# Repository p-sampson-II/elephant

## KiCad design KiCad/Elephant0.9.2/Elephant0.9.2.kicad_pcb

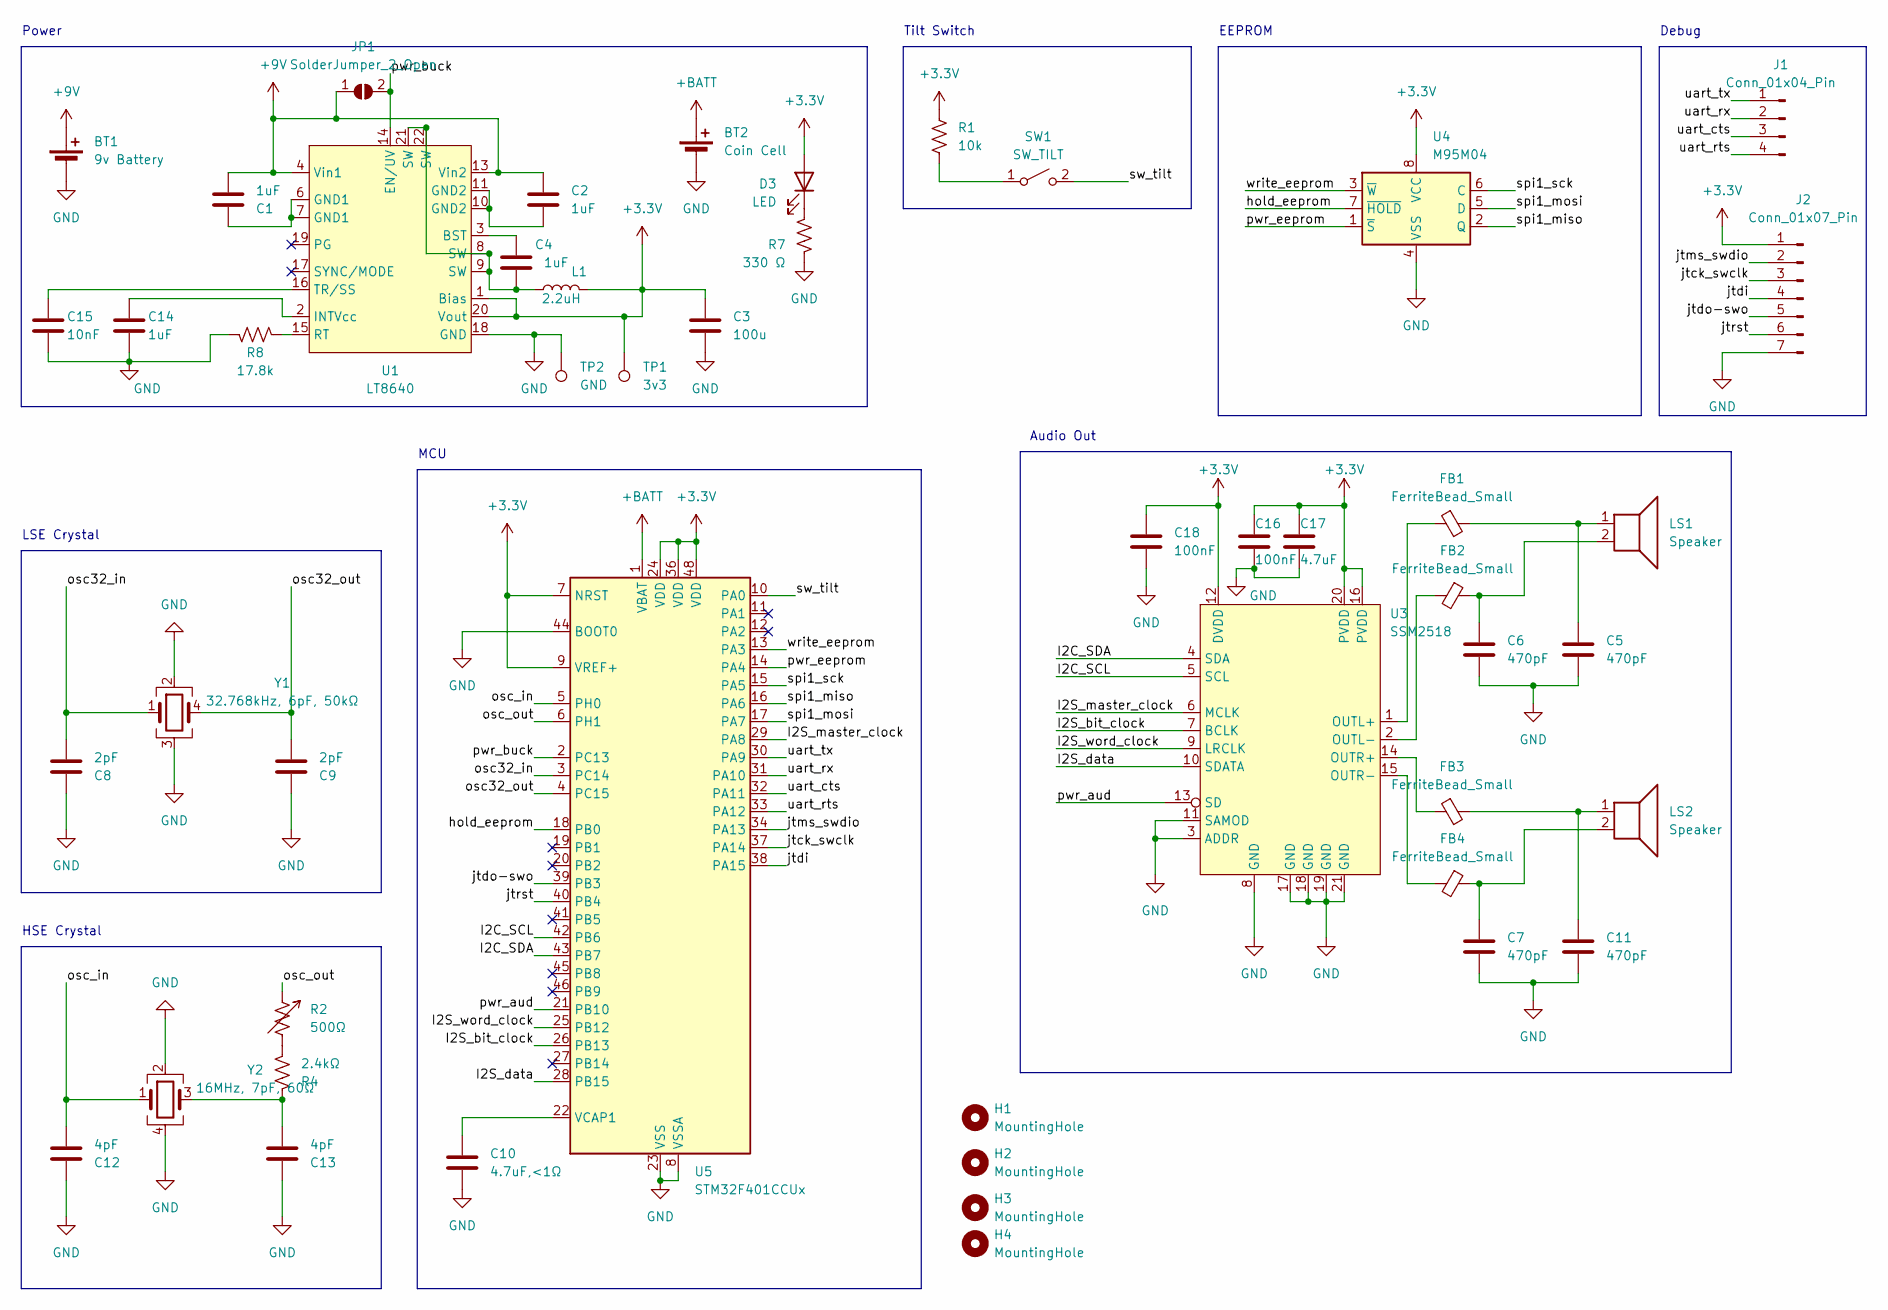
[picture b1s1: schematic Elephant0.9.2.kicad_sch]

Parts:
BT1: 9v Battery; JST_PH_B2B-PH-K_1x02_P2.00mm_Vertical
BT2: Coin Cell; BatteryHolder_Keystone_1057_1x2032
C1, C2, C4, C14: 1uF; C_0603_1608Metric
C3: 100u; Capacitor SMD 2917 (7343 Metric)
C5, C6, C7, C11: 470pF; C_0603_1608Metric
C8, C9: 2pF; C_0603_1608Metric
C10: 4.7uF,<1Ω; 1411 (3528 Metric)
C12, C13: 4pF; C_0603_1608Metric
C15: 10nF; C_0603_1608Metric
C16, C18: 100nF; C_0603_1608Metric
C17: 4.7uF; C_0603_1608Metric
D3: LED; LED_0603_1608Metric
FB1, FB2, FB3, FB4: FerriteBead_Small; L_0402_1005Metric
H1, H2, H3, H4: MountingHole; MountingHole_2.7mm_M2.5
J1: Conn_01x04_Pin; JST_PH_B4B-PH-K_1x04_P2.00mm_Vertical
J2: Conn_01x07_Pin; JST_PH_B7B-PH-K_1x07_P2.00mm_Vertical
JP1: SolderJumper_2_Open; SolderJumper-2_P1.3mm_Open_Pad1.0x1.5mm
L1: 2.2uH; L_Bourns-SRN8040_8x8.15mm
LS1, LS2: Speaker; JST_PH_B2B-PH-K_1x02_P2.00mm_Vertical
R1: 10k; R_0603_1608Metric
R2: 500Ω; TC42 – 2 mm SMD Trimpot - Bournes
R4: 2.4kΩ; R_0603_1608Metric
R7: 330 Ω; R_0603_1608Metric
R8: 17.8k; R_0603_1608Metric
SW1: SW_TILT; PinHeader_1x02_P2.54mm_Vertical
TP1: 3v3; TestPoint_Pad_D1.0mm
TP2: GND; TestPoint_Pad_D1.0mm
U1: LT8640
U3: SSM2518; QFN-20-1EP_4x4mm_P0.5mm_EP2.5x2.5mm
U4: M95M04; TSSOP-8_4.4x3mm_P0.65mm
U5: STM32F401CCUx; QFN-48-1EP_7x7mm_P0.5mm_EP5.6x5.6mm
Y1: 32.768kHz, 6pF, 50kΩ; Crystal_SMD_Abracon_ABS25-4Pin_8.0x3.8mm
Y2: 16MHz, 7pF, 60Ω; Crystal_SMD_3225-4Pin_3.2x2.5mm

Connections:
+3.3V: C3.1, C16.1, C17.1, C18.1, D3.2 (A), J2.1, L1.2, R1.1, TP1.1, U1.1 (Bias), U1.20 (Vout), U3.12 (DVDD), U3.16 (PVDD), U3.20 (PVDD), U4.8 (VCC), U5.7 (NRST), U5.9 (VREF+), U5.24 (VDD), U5.36 (VDD), U5.48 (VDD)
+9V: BT1.1 (+), C1.2, C2.1, JP1.1 (A), U1.4 (Vin1), U1.13 (Vin2)
+BATT: BT2.1 (+), U5.1 (VBAT)
/I2C_SCL: U3.5 (SCL), U5.42 (PB6)
/I2C_SDA: U3.4 (SDA), U5.43 (PB7)
/I2S_bit_clock: U3.7 (BCLK), U5.26 (PB13)
/I2S_data: U3.10 (SDATA), U5.28 (PB15)
/I2S_master_clock: U3.6 (MCLK), U5.29 (PA8)
/I2S_word_clock: U3.9 (LRCLK), U5.25 (PB12)
/hold_eeprom: U4.7 (~HOLD), U5.18 (PB0)
/jtck_swclk: J2.3, U5.37 (PA14)
/jtdi: J2.4, U5.38 (PA15)
/jtdo-swo: J2.5, U5.39 (PB3)
/jtms_swdio: J2.2, U5.34 (PA13)
/jtrst: J2.6, U5.40 (PB4)
/osc32_in: C8.2, U5.3 (PC14), Y1.1
/osc32_out: C9.2, U5.4 (PC15), Y1.4
/osc_in: C12.2, U5.5 (PH0), Y2.1
/osc_out: R2.1, U5.6 (PH1)
/pwr_aud: U3.13 (SD), U5.21 (PB10)
/pwr_buck: JP1.2 (B), U1.14 (EN/UV), U5.2 (PC13)
/pwr_eeprom: U4.1 (~S), U5.14 (PA4)
/spi1_miso: U4.2 (Q), U5.16 (PA6)
/spi1_mosi: U4.5 (D), U5.17 (PA7)
/spi1_sck: U4.6 (C), U5.15 (PA5)
/sw_tilt: SW1.2 (B), U5.10 (PA0)
/uart_cts: J1.3, U5.32 (PA11)
/uart_rts: J1.4, U5.33 (PA12)
/uart_rx: J1.2, U5.31 (PA10)
/uart_tx: J1.1, U5.30 (PA9)
/write_eeprom: U4.3 (~W), U5.13 (PA3)
GND: BT1.2 (-), BT2.2 (-), C3.2, C5.2, C6.2, C7.2, C8.1, C9.1, C10.2, C11.2, C12.1, C13.1, C14.2, C15.2, C16.2, C17.2, C18.2, J2.7, R7.2, R8.2, TP2.1, U1.18 (GND), U3.3 (ADDR), U3.8 (GND), U3.11 (SAMOD), U3.17 (GND), U3.18 (GND), U3.19 (GND), U3.21 (GND), U4.4 (VSS), U5.8 (VSSA), U5.23 (VSS), U5.35 (VSS), U5.44 (BOOT0), U5.47 (VSS), U5.49 (VSS), Y1.2, Y1.3, Y2.2, Y2.4
unnamed: C1.1, U1.6 (GND1), U1.7 (GND1)
unnamed: C2.2, U1.10 (GND2), U1.11 (GND2)
unnamed: C4.2, L1.1, U1.8 (SW), U1.9 (SW), U1.21 (SW), U1.22 (SW)
unnamed: C5.1, FB1.2, LS1.1
unnamed: C6.1, FB2.1, LS1.2
unnamed: C7.1, FB4.1, LS2.2
unnamed: C11.1, FB3.2, LS2.1
unnamed: C13.2, R4.1, Y2.3
unnamed: D3.1 (K), R7.1
unnamed: R2.2, R4.2
unnamed: R1.2, SW1.1 (A)
unnamed: C4.1, U1.3 (BST)
unnamed: C14.1, U1.2 (INTVcc)
unnamed: R8.1, U1.15 (RT)
unnamed: C15.1, U1.16 (TR/SS)
unnamed: FB1.1, U3.1 (OUTL+)
unnamed: FB2.2, U3.2 (OUTL-)
unnamed: FB3.1, U3.14 (OUTR+)
unnamed: FB4.2, U3.15 (OUTR-)
unnamed: C10.1, U5.22 (VCAP1)

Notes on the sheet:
HSE Crystal
MCU
Power
Debug
Audio Out
EEPROM
Tilt Switch
LSE Crystal

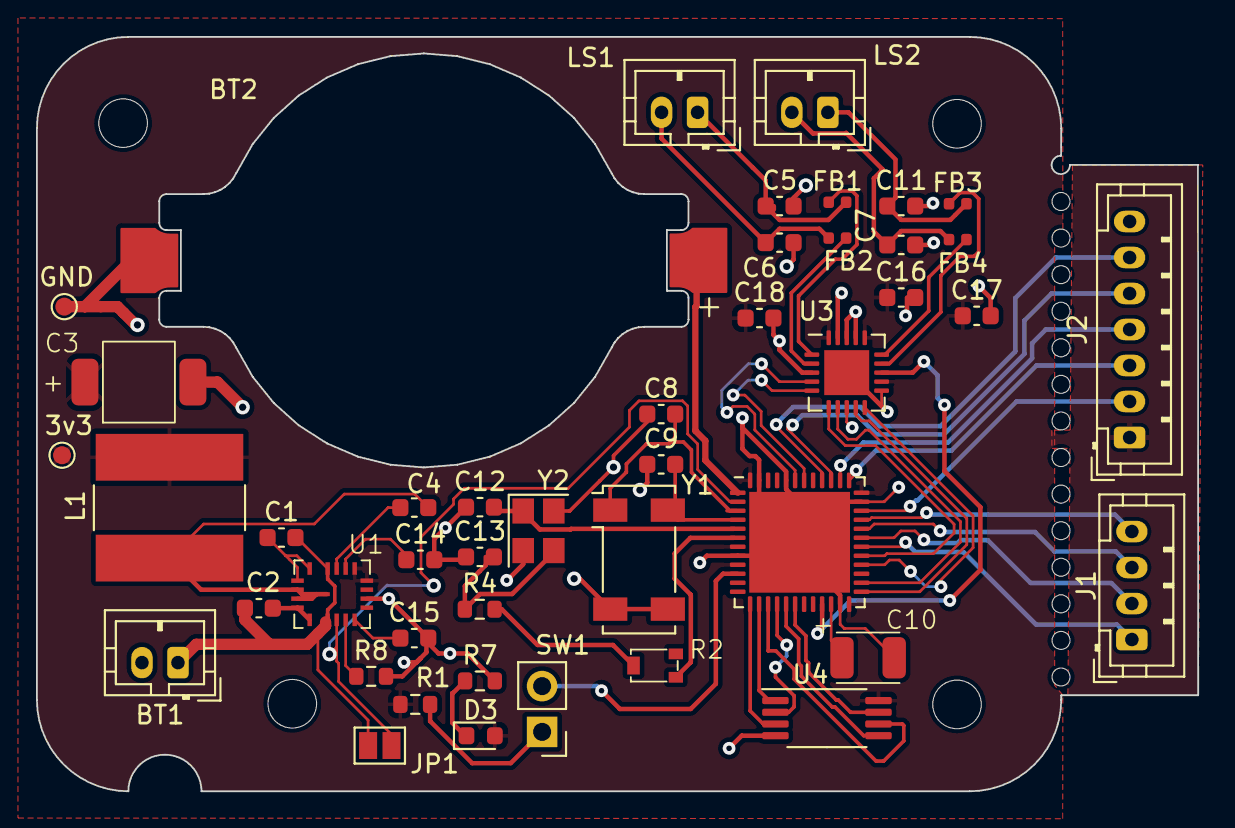
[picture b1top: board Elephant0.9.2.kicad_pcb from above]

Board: 2 copper layers, 64.5 x 41.9 mm, 49 parts (0 on the bottom side), 52 nets.

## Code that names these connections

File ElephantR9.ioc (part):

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Mcu.Name=STM32F401C(B-C)Ux
Mcu.Package=UFQFPN48
Mcu.UserName=STM32F401CCUx
PA0-WKUP.GPIOParameters=GPIO_Label
PA0-WKUP.GPIO_Label=sw_tilt
PA0-WKUP.Mode=SYS_WakeUp0
PA0-WKUP.Signal=SYS_WKUP
PA1.GPIOParameters=GPIO_Label
PA1.GPIO_Label=ld_heartbeat
PA1.Signal=GPIO_Output
PA10.Mode=Asynchronous
PA10.Signal=USART1_RX
PA11.Mode=CTS_RTS
PA11.Signal=USART1_CTS
PA12.Mode=CTS_RTS
PA12.Signal=USART1_RTS
PA13.Mode=JTAG_5_pins
PA13.Signal=SYS_JTMS-SWDIO
PA14.Mode=JTAG_5_pins
PA14.Signal=SYS_JTCK-SWCLK
PA15.Mode=JTAG_5_pins
PA15.Signal=SYS_JTDI
PA3.GPIOParameters=GPIO_Label
PA3.GPIO_Label=pwr_eeprom
PA3.Signal=GPIO_Output
PA4.GPIOParameters=GPIO_Label
PA4.GPIO_Label=write_eeprom
PA4.Signal=GPIO_Output
PA5.Mode=Full_Duplex_Master
PA5.Signal=SPI1_SCK
PA6.Mode=Full_Duplex_Master
PA6.Signal=SPI1_MISO
PA7.Mode=Full_Duplex_Master
PA7.Signal=SPI1_MOSI
PA8.Mode=Clock-out-1
PA8.Signal=RCC_MCO_1
PA9.Mode=Asynchronous
PA9.Signal=USART1_TX
PB0.GPIOParameters=GPIO_Label
PB0.GPIO_Label=hold_eeprom
PB0.Signal=GPIO_Output
PB10.GPIOParameters=GPIO_Label
PB10.GPIO_Label=pwr_aud
PB10.Signal=GPIO_Output
PB12.Mode=Half_Duplex_Master
PB12.Signal=I2S2_WS
PB13.Mode=Half_Duplex_Master
PB13.Signal=I2S2_CK
PB15.Mode=Half_Duplex_Master
PB15.Signal=I2S2_SD
PB3.Mode=JTAG_5_pins
PB3.Signal=SYS_JTDO-SWO
PB4.Mode=JTAG_5_pins
PB4.Signal=SYS_JTRST
PB6.Mode=I2C
PB6.Signal=I2C1_SCL
PB7.Mode=I2C
PB7.Signal=I2C1_SDA
PC13-ANTI_TAMP.Mode=AlarmA_RoutedAF
PC13-ANTI_TAMP.Signal=RTC_AF1
PC14-OSC32_IN.Mode=LSE-External-Oscillator
PC14-OSC32_IN.Signal=RCC_OSC32_IN
PC15-OSC32_OUT.Mode=LSE-External-Oscillator
PC15-OSC32_OUT.Signal=RCC_OSC32_OUT
PH0\ -\ OSC_IN.Mode=HSE-External-Oscillator
PH0\ -\ OSC_IN.Signal=RCC_OSC_IN
PH1\ -\ OSC_OUT.Mode=HSE-External-Oscillator
PH1\ -\ OSC_OUT.Signal=RCC_OSC_OUT
RCC.HSE_VALUE=25000000
RCC.SYSCLKFreq_VALUE=84000000
RCC.SYSCLKSource=RCC_SYSCLKSOURCE_PLLCLK
board=custom

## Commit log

2024-01-03 STM32 Files
2024-01-03 vscode.
2024-01-03 KiCad files
2024-01-04 Added HALs from CubeMX Began to describe possible system states in concrete_elephant_states.cpp
2024-01-04 Added Intermediate and App sources and headers to Makefile Created intermediate audio abstraction class
2024-02-07 Added the audio system with a way to test it.
